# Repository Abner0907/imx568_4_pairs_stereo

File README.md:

# IMX568 4-stereo-pair VIO camera system for Jetson AGX Xavier

Four hardware-synchronized stereo pairs (8 × Sony IMX568-AAMJ-C, 5.1 MP mono global shutter):

* **4 identical stereo boards.** Each carries two IMX568 on a rigid 80 mm baseline (configurable). A CrossLink-NX FPGA merges left/right into one x4 CSI-2 port (VC0/VC1).
* **4 FPC cables** (40-pin, 0.5 mm) run to an **AGX adapter board**. It plugs into the Xavier devkit camera connector (Samtec QTH-060) and uses all 16 CSI lanes.
* **An RP2040 sync controller** on the adapter triggers each pair. All pairs share a common mid-exposure, and a SYNC_OUT edge timestamps every 8-frame set on the Xavier.

Variant B (GMSL2 coax heads + MAX9296A carrier) is kept for camera runs longer than ~30 cm.

```
docs/
  01_system_architecture.md     overview, Xavier lane/VC/I2C map, bandwidth, sync, power, verification status
  02_stereo_board_design.md     stereo board: sensors, FPGA, power, clock, mechanics
  03_fpc_and_xavier_adapter.md  FPC pinout/spec, AGX connector pin map, adapter circuits + layout rules
  04_pcb_layout_guidelines.md   the 3 generated layouts, stack-up, LGA assembly, routing rules
  05_bringup_and_sync.md        build/install, bring-up checklist, sync proof, VIO timestamps
  variant_b_gmsl/               GMSL2 camera head + deserializer carrier (long cables)
hardware/
  tools/imx568_data.py          single source of truth: 132-pin table, nets, datasheet decoupling
  tools/kicadgen.py             KiCad board generator library (fan-out, decoupling, routing, mini-DRC, preview)
  tools/gen_kicad.py            -> symbol, footprint, stereo_board, camera_head_gmsl  (--baseline mm)
  tools/gen_adapter.py          -> adapter_board + hardware/adapter/*.csv
  tools/gen_netlist.py          -> hardware/stereo_board/*.csv, hardware/camera_head_gmsl/*.csv
  tools/fpc_pinout.py           40-pin FPC pinout
  tools/xavier_cam_connector.py AGX camera connector pin map (from Antmicro, Apache-2.0)
  kicad/                        IMX568.kicad_sym, IMX568.pretty/, stereo_board/, adapter_board/, camera_head_gmsl/
  stereo_board/ adapter/ camera_head_gmsl/   netlists, pin maps, BOMs (CSV)
fpga/                           stereo_ctrl.v (sequencing/trigger/status) + simulated testbench
driver/
  kernel/nv_imx568.c            tegracam driver: default = stereo board/FPC, `make GMSL=1` = variant B
  kernel/imx568_mode_tbls.h     register tables (documented regs filled; NDA tables to fill)
  dts/gen_dtsi_fpc.py           -> tegra194-camera-imx568-fpc-8cam.dtsi  (variant A)
  dts/gen_dtsi.py               -> tegra194-camera-imx568-gmsl-8cam.dtsi (variant B)
firmware/sync_controller/       RP2040 PIO trigger generator (per-pair exposure, common mid-exposure, SYNC_OUT)
software/sync_capture/          C++17 V4L2 + GPIO capture -> synchronized 8-frame sets (+ unit test)
```

Regenerate everything:
```bash
python3 hardware/tools/gen_kicad.py --baseline 80   # exit 1 on any mini-DRC violation
python3 hardware/tools/gen_adapter.py
python3 hardware/tools/gen_netlist.py
python3 driver/dts/gen_dtsi_fpc.py && python3 driver/dts/gen_dtsi.py
```

## Status

| Part | State |
|---|---|
| Stereo board layout demo | 2 sensors fully fanned out + decoupled, 10 CSI pairs routed to the FPGA; 0 mini-DRC violations |
| Adapter | Xavier connector map (from proven open hardware), FPC↔Xavier netlist, layout demo with the 4 FPC sockets |
| FPGA control logic | Simulated with Icarus Verilog: testbench passes, mutation test caught |
| CSI-2 VC merge | Lattice reference design (to configure in Radiant) |
| Driver | FPC and GMSL builds compile warning-free (`W=1`) against kernel headers with stub NVIDIA headers; not yet run on hardware |
| Device trees | Both compile with dtc (8 sensors) |
| Sync firmware / capture tool | Firmware type-checked (no Pico SDK here); tool builds, unit test passes |
| **Blocking for first image** | IMX568 NDA register tables (PLL/INCK, readout mode, initial settings) |
| **Verify before layout release** | CrossLink-NX package + D-PHY ball assignment + supply rails; 2.9 V LDO option; 1.8 V EN compatibility of the 5 V switches; Xavier GPIO behind CAM1_RST/GPIO10 |

The IMX568 datasheet in this folder is marked **Confidential** (Sony). Keep it, and anything copied from it, out of public repositories.

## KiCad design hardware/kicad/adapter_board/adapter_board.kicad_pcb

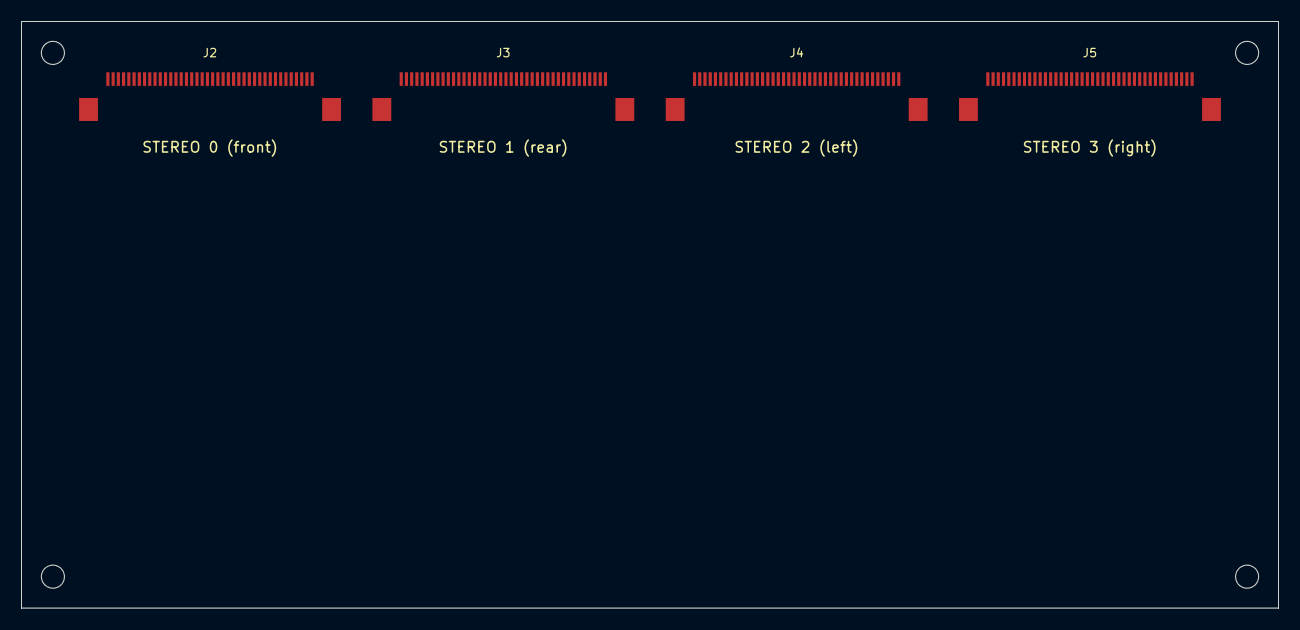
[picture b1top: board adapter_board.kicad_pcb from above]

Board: 6 copper layers, 120.0 x 56.0 mm, 8 parts (0 on the bottom side), 5 nets, no tracks yet.

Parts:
H1, H2, H3, H4: M2; MountingHole_2.2mm_M2
J2, J3, J4, J5: FH12-40S-0.5SH(55); Hirose_FH12-40S-0.5SH_1x40-1MP_P0.50mm_Horizontal

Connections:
GND: J2.1, J2.4, J2.7, J2.10, J2.13, J2.16, J2.19, J2.21, J2.26, J2.29, J2.30, J2.35, J2.36, J2.37, J2.38, J2.40, J2.MP, J3.1, J3.4, J3.7, J3.10, J3.13, J3.16, J3.19, J3.21, J3.26, J3.29, J3.30, J3.35, J3.36, J3.37, J3.38, J3.40, J3.MP, J4.1, J4.4, J4.7, J4.10, J4.13, J4.16, J4.19, J4.21, J4.26, J4.29, J4.30, J4.35, J4.36, J4.37, J4.38, J4.40, J4.MP, J5.1, J5.4, J5.7, J5.10, J5.13, J5.16, J5.19, J5.21, J5.26, J5.29, J5.30, J5.35, J5.36, J5.37, J5.38, J5.40, J5.MP
S0_VIN_5V: J2.31, J2.32, J2.33, J2.34
S1_VIN_5V: J3.31, J3.32, J3.33, J3.34
S2_VIN_5V: J4.31, J4.32, J4.33, J4.34
S3_VIN_5V: J5.31, J5.32, J5.33, J5.34

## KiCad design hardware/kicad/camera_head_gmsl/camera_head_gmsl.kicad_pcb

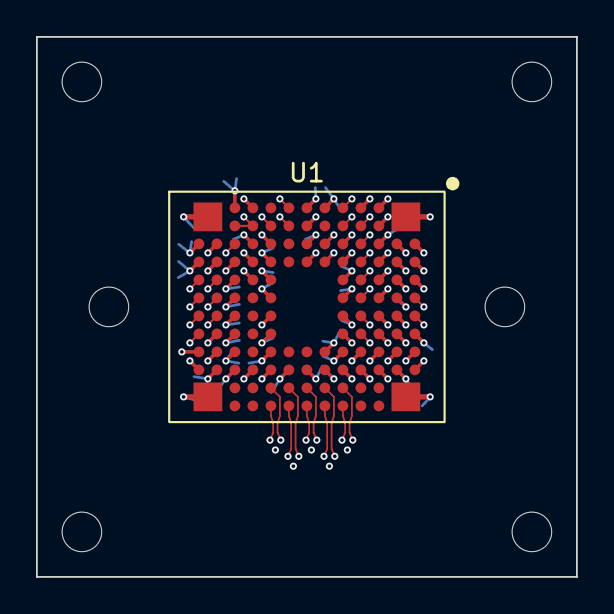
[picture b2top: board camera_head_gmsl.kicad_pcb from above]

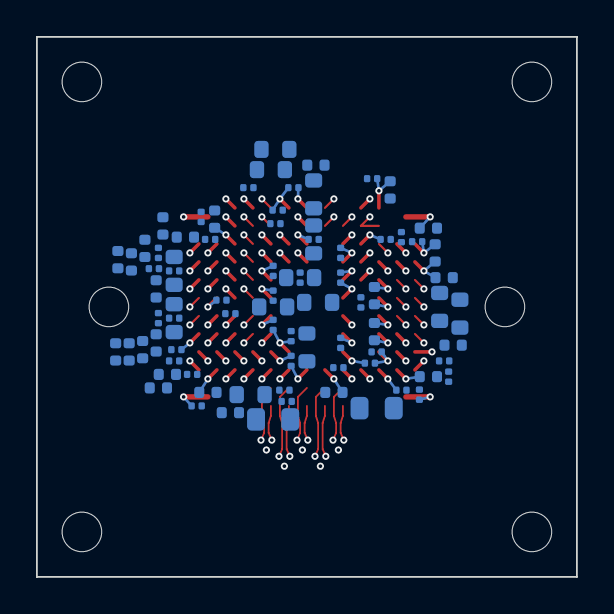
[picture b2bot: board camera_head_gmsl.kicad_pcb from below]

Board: 6 copper layers, 30.0 x 30.0 mm, 88 parts (81 on the bottom side), 10 nets.

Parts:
C1, C2, C3, C4, C7, C9, C11, C13, C15, C17, C19, C21, C23, C24, C26, C29, C30, C31, C32, C37, C39, C41, C43, C45, C47, C49, C51, C53, C55, C58, C59, C62, C63, C65, C68, C70, C72, C75: 0.1u; C_0201
C5, C6, C25, C52, C57: 22u; C_0603
C8, C10, C12, C14, C16, C18, C20, C22: 10u; C_0603
C27, C28, C36, C38, C40, C42, C44, C46, C48, C50, C54, C56, C61, C64, C66, C67, C76, C77, C78, C79: 4.7u; C_0402
C33, C34, C35, C60, C74: 1u; C_0402
C69, C71, C73: 1n; C_0201
H1, H2, H3, H4, H5, H6: M2; MountingHole_2.2mm_M2
L80, L81: 10uH; C_0805
U1: IMX568-AAMJ-C; IMX568_LGA132

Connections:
+1V1: C36.1, C37.1, C38.1, C39.1, C40.1, C41.1, C42.1, C43.1, C44.1, C45.1, C46.1, C47.1, C48.1, C49.1, C50.1, C51.1, C52.1, C53.1, C54.1, C55.1, C56.1, C57.1, C58.1, C59.1, C60.1, C61.1, C62.1, C63.1, C64.1, C65.1, C66.1, C70.1, C71.1, L80.1, L81.1, U1.A3, U1.A10, U1.B3, U1.C6, U1.C7, U1.D1, U1.G1, U1.G4, U1.H10, U1.J5, U1.L1, U1.L5, U1.M3, U1.M9, U1.N3, U1.N10
+1V1_LIF: C72.1, C73.1, L80.2, U1.F10, U1.K10
+1V1_PLA: C67.1, C68.1, C69.1, L81.2, U1.L7, U1.L9
+1V8_SNS: C74.1, C75.1, U1.N9
+2V9: C23.1, C24.1, C25.1, C26.1, C27.1, C28.1, C29.1, C30.1, C31.1, C32.1, C33.1, C34.1, C35.1, U1.A5, U1.A8, U1.A9, U1.F4, U1.K4
+3V3A: C1.1, C2.1, C3.1, C4.1, C5.1, C6.1, C7.1, C8.1, C9.1, C10.1, C11.1, C12.1, C13.1, C14.1, C15.1, C16.1, C17.1, C18.1, C19.1, C20.1, C21.1, C22.1, U1.C4, U1.C5, U1.C8, U1.E3, U1.E4, U1.E5, U1.E6, U1.E7, U1.E8, U1.E9, U1.J4, U1.J7, U1.J8
GND: C1.2, C2.2, C3.2, C4.2, C5.2, C6.2, C7.2, C8.2, C9.2, C10.2, C11.2, C12.2, C13.2, C14.2, C15.2, C16.2, C17.2, C18.2, C19.2, C20.2, C21.2, C22.2, C23.2, C24.2, C25.2, C26.2, C27.2, C28.2, C29.2, C30.2, C31.2, C32.2, C33.2, C34.2, C35.2, C36.2, C37.2, C38.2, C39.2, C40.2, C41.2, C42.2, C43.2, C44.2, C45.2, C46.2, C47.2, C48.2, C49.2, C50.2, C51.2, C52.2, C53.2, C54.2, C55.2, C56.2, C57.2, C58.2, C59.2, C60.2, C61.2, C62.2, C63.2, C64.2, C65.2, C66.2, C67.2, C68.2, C69.2, C70.2, C71.2, C72.2, C73.2, C74.2, C75.2, C76.2, C77.2, C78.2, C79.2, U1.A1, U1.A4, U1.A12, U1.B4, U1.B5, U1.B6, U1.B7, U1.B8, U1.B9, U1.B10, U1.C1, U1.C2, U1.C3, U1.C9, U1.C10, U1.D9, U1.D10, U1.E10, U1.F1, U1.F3, U1.F9, U1.G2, U1.G3, U1.G10, U1.J3, U1.J6, U1.J9, U1.J10, U1.K1, U1.K3, U1.K5, U1.L4, U1.L6, U1.L8, U1.L10, U1.M4, U1.M8, U1.M10, U1.N1, U1.N4, U1.N12
SNS_SLAMODE: U1.H2, U1.K2, U1.L2
VCP1: C76.1, C77.1, U1.A7, U1.D8
VCP2: C78.1, C79.1, U1.A6, U1.D3, U1.D4, U1.D5, U1.D6, U1.D7
